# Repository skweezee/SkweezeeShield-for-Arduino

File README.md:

# Arduino

Including the Skweezee Sensing Shield for Arduino.

All components of the shield for Arduino are available as open source hardware (licensed under CC BY-SA 4.0) and software (copyrighted by KU Leuven and licensed under MIT license).

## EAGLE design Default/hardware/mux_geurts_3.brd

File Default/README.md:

Default Skweezee sensing shield for Arduino Uno, using a UTP cable (8 wires) resulting in 28 dimensions.

This default shield connects to an Arduino Uno through pins:

*   7,  8,  9 (select lines of MUX 1)
*  10, 11, 12 (select lines of MUX 2)
*  13 (enable MUX 1 & MUX 2)
*  AO (value)

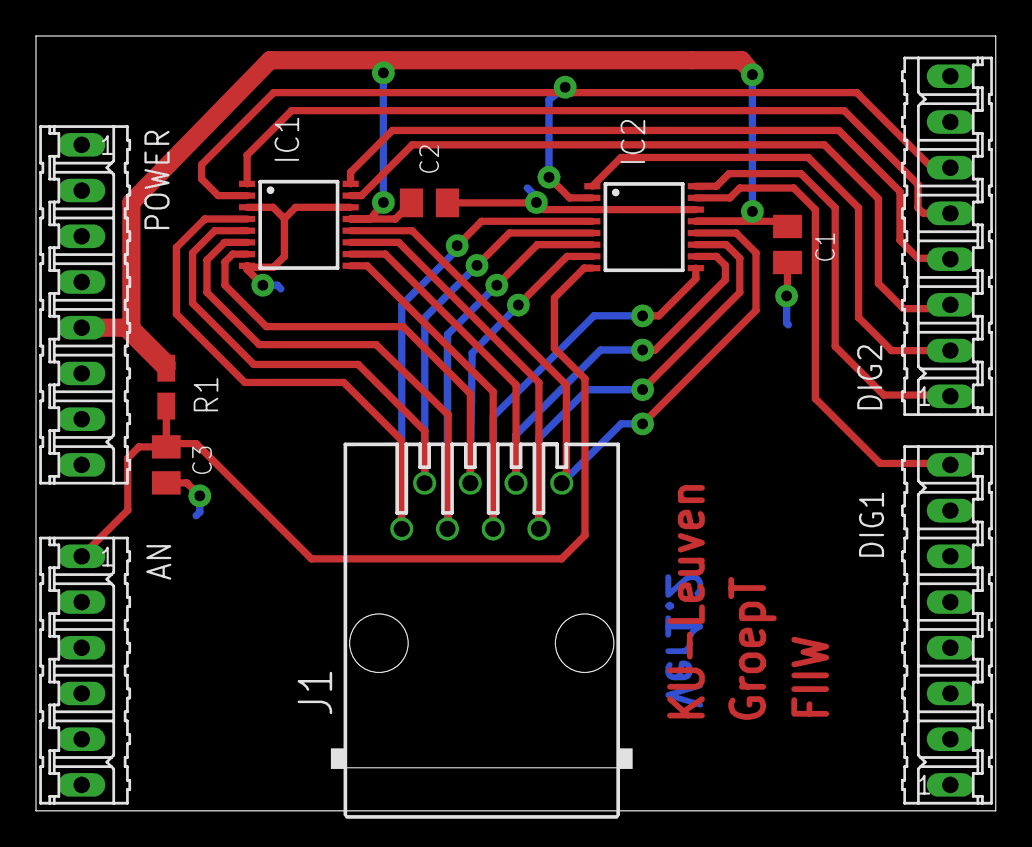
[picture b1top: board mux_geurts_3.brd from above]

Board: 2 copper layers, 53.3 x 43.0 mm, 11 parts (0 on the bottom side), 18 nets.

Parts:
AN: 06P
C1, C2: 100n; C0805K
C3: 33p; C0805K
DIG1, DIG2: 08P
IC1, IC2: ADG608RU; TSSOP16
J1: 520251-4
POWER: 08P
R1: 180; R0805W

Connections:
+5V: C1.1, C2.1, IC1.13, IC2.13, POWER.5, R1.1
GND: C1.2, C2.2, C3.2, DIG2.7, IC1.3, IC1.8, IC1.14, IC2.3, IC2.14, POWER.6, POWER.7
unnamed: DIG2.2, IC2.1
unnamed: DIG2.1, IC2.16
unnamed: DIG1.8, IC2.15
unnamed: DIG2.5, IC1.1
unnamed: DIG2.4, IC1.16
unnamed: DIG2.3, IC1.15
unnamed: AN.1, C3.1, IC2.8, R1.2
unnamed: DIG2.6, IC1.2, IC2.2
S1: IC1.4, IC2.4, J1.1
S2: IC1.5, IC2.5, J1.2
S3: IC1.6, IC2.6, J1.3
S4: IC1.7, IC2.7, J1.4
S5: IC1.12, IC2.12, J1.8
S6: IC1.11, IC2.11, J1.7
S7: IC1.10, IC2.10, J1.6
S8: IC1.9, IC2.9, J1.5

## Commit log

2019-03-19 Create LICENSE
    software license
2019-03-19 v2014
2019-03-19 Create LICENSE
    Hardware license (CC BY-SA 4.0)
2019-03-19 Rename Skweezee.ino to software.ino
2019-05-29 Rename software.ino to Default/software.ino
2019-05-29 Default shield
2019-05-29 Rename README to README.md
